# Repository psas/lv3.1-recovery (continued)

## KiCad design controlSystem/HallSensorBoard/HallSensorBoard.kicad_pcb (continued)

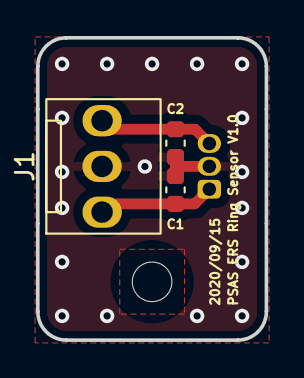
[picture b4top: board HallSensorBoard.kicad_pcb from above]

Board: 2 copper layers, 12.7 x 16.8 mm, 4 parts (1 on the bottom side), 3 nets.

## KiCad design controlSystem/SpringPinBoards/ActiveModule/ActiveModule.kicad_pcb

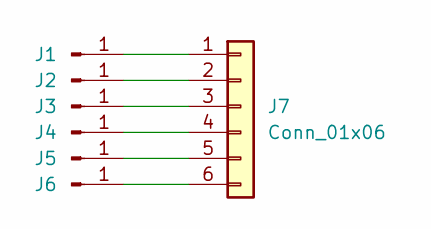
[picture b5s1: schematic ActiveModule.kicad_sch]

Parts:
J1, J2, J3, J4, J5, J6: Conn_01x01_Male; Mill-Max-0921-5-15-20-77-14-11-0
J7: Conn_01x06; PinHeader_1x06_P2.00mm_Vertical

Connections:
unnamed: J1.1, J7.1
unnamed: J2.1, J7.2
unnamed: J3.1, J7.3
unnamed: J4.1, J7.4
unnamed: J5.1, J7.5
unnamed: J6.1, J7.6

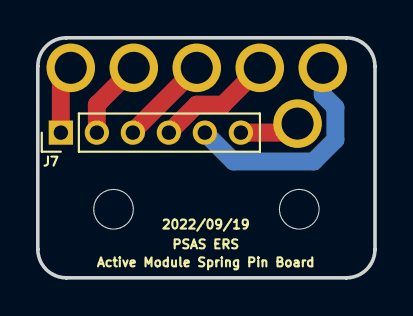
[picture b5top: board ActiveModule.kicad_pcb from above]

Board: 2 copper layers, 18.7 x 13.3 mm, 7 parts (0 on the bottom side), 6 nets.

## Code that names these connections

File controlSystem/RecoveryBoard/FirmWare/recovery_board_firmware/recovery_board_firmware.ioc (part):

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Mcu.Name=STM32F042K(4-6)Tx
Mcu.Package=LQFP32
Mcu.UserName=STM32F042K6Tx
PA1.GPIOParameters=GPIO_Label
PA1.GPIO_Label=LA_POS
PA1.Mode=IN1
PA1.Signal=ADC_IN1
PA11.Mode=Master
PA11.Signal=CAN_RX
PA12.Mode=Master
PA12.Signal=CAN_TX
PA13.Mode=Serial_Wire
PA13.Signal=SYS_SWDIO
PA14.Mode=Serial_Wire
PA14.Signal=SYS_SWCLK
PA15.GPIOParameters=GPIO_ModeDefaultPP,GPIO_Speed,GPIO_PuPd
PA15.GPIO_ModeDefaultPP=GPIO_MODE_AF_PP
PA15.GPIO_PuPd=GPIO_NOPULL
PA15.GPIO_Speed=GPIO_SPEED_FREQ_HIGH
PA15.Mode=Asynchronous
PA15.Signal=USART2_RX
PA2.GPIOParameters=GPIO_ModeDefaultPP,GPIO_Speed,GPIO_PuPd
PA2.GPIO_ModeDefaultPP=GPIO_MODE_AF_PP
PA2.GPIO_PuPd=GPIO_NOPULL
PA2.GPIO_Speed=GPIO_SPEED_FREQ_HIGH
PA2.Mode=Asynchronous
PA2.Signal=USART2_TX
PA3.GPIOParameters=GPIO_PuPd,GPIO_Label,GPIO_Mode
PA3.GPIO_Label=ISO_CHUTE
PA3.GPIO_Mode=GPIO_MODE_INPUT
PA3.GPIO_PuPd=GPIO_NOPULL
PA3.Signal=GPIO_Input
PA4.GPIOParameters=GPIO_PuPd,GPIO_Label,GPIO_Mode
PA4.GPIO_Label=ISO_DROGUE
PA4.GPIO_Mode=GPIO_MODE_INPUT
PA4.GPIO_PuPd=GPIO_NOPULL
PA4.Signal=GPIO_Input
PA5.GPIOParameters=GPIO_Speed,PinState,GPIO_PuPd,GPIO_Label,GPIO_ModeDefaultOutputPP
PA5.GPIO_Label=DCM_DIR
PA5.GPIO_ModeDefaultOutputPP=GPIO_MODE_OUTPUT_PP
PA5.GPIO_PuPd=GPIO_NOPULL
PA5.GPIO_Speed=GPIO_SPEED_FREQ_LOW
PA5.PinState=GPIO_PIN_RESET
PA5.Signal=GPIO_Output
PA6.GPIOParameters=GPIO_Label
PA6.GPIO_Label=DCM_PWM
PA6.Signal=S_TIM3_CH1
PA7.GPIOParameters=GPIO_Speed,PinState,GPIO_PuPd,GPIO_Label,GPIO_ModeDefaultOutputPP
PA7.GPIO_Label=DCM_ON
PA7.GPIO_ModeDefaultOutputPP=GPIO_MODE_OUTPUT_PP
PA7.GPIO_PuPd=GPIO_NOPULL
PA7.GPIO_Speed=GPIO_SPEED_FREQ_LOW
PA7.PinState=GPIO_PIN_RESET
PA7.Signal=GPIO_Output
PA8.GPIOParameters=GPIO_Speed,PinState,GPIO_PuPd,GPIO_Label,GPIO_ModeDefaultOutputPP
PA8.GPIO_Label=LA_IN1
PA8.GPIO_ModeDefaultOutputPP=GPIO_MODE_OUTPUT_PP
PA8.GPIO_PuPd=GPIO_NOPULL
PA8.GPIO_Speed=GPIO_SPEED_FREQ_LOW
PA8.PinState=GPIO_PIN_RESET
PA8.Signal=GPIO_Output
PA9.GPIOParameters=GPIO_Speed,GPIO_FMA9,PinState,GPIO_PuPd,GPIO_Label,GPIO_ModeDefaultOutputPP
PA9.GPIO_FMA9=__NULL
PA9.GPIO_Label=LA_IN2
PA9.GPIO_ModeDefaultOutputPP=GPIO_MODE_OUTPUT_PP
PA9.GPIO_PuPd=GPIO_NOPULL
PA9.GPIO_Speed=GPIO_SPEED_FREQ_LOW
PA9.PinState=GPIO_PIN_RESET
PA9.Signal=GPIO_Output
PB0.GPIOParameters=GPIO_Speed,PinState,GPIO_PuPd,GPIO_Label,GPIO_ModeDefaultOutputPP
PB0.GPIO_Label=LED
PB0.GPIO_ModeDefaultOutputPP=GPIO_MODE_OUTPUT_PP
PB0.GPIO_PuPd=GPIO_NOPULL
PB0.GPIO_Speed=GPIO_SPEED_FREQ_LOW
PB0.PinState=GPIO_PIN_RESET
PB0.Signal=GPIO_Output
PB1.GPIOParameters=GPIO_Label
PB1.GPIO_Label=BATT_READ
PB1.Mode=IN9
PB1.Signal=ADC_IN9
PB3.GPIOParameters=GPIO_Speed,PinState,GPIO_PuPd,GPIO_Label,GPIO_ModeDefaultOutputPP
PB3.GPIO_Label=SENSOR_ON
PB3.GPIO_ModeDefaultOutputPP=GPIO_MODE_OUTPUT_PP
PB3.GPIO_PuPd=GPIO_NOPULL
PB3.GPIO_Speed=GPIO_SPEED_FREQ_LOW
PB3.PinState=GPIO_PIN_RESET
PB3.Signal=GPIO_Output
PB4.GPIOParameters=GPIO_Label
PB4.GPIO_Label=SENSOR2
PB4.Signal=GPIO_Input
PB5.GPIOParameters=GPIO_PuPd,GPIO_Label,GPIO_Mode
PB5.GPIO_Label=SENSOR1
PB5.GPIO_Mode=GPIO_MODE_INPUT
PB5.GPIO_PuPd=GPIO_NOPULL
PB5.Signal=GPIO_Input
PB7.GPIOParameters=GPIO_Speed,PinState,GPIO_PuPd,GPIO_Label,GPIO_ModeDefaultOutputPP,GPIO_FM7
PB7.GPIO_FM7=__NULL
PB7.GPIO_Label=ACOK
PB7.GPIO_ModeDefaultOutputPP=GPIO_MODE_OUTPUT_PP
PB7.GPIO_PuPd=GPIO_NOPULL
PB7.GPIO_Speed=GPIO_SPEED_FREQ_LOW
PB7.PinState=GPIO_PIN_RESET
PB7.Signal=GPIO_Output
PB8.GPIOParameters=GPIO_Label
PB8.GPIO_Label=SPKR
PB8.Signal=S_TIM16_CH1
PF0-OSC_IN.Mode=HSE-External-Clock-Source
PF0-OSC_IN.Signal=RCC_OSC_IN
RCC.SYSCLKFreq_VALUE=8000000
board=NUCLEO-F042K6
boardIOC=true

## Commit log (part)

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2025-10-31 Fix bug in can_reader
    The conditional compilation scope should be around this entire arm of
    the match statement, otherwise the main board will send out the drogue
    acknowledgement message
2025-10-31 Rename TELEMETRUM_HEARTBEAT_ID -> SENDER_HEARTBEAT_ID
    It's not the telemetrum that sends the heartbeat its the sender board
2025-11-01 Write README for src/bin
2025-11-01 Rename *_STATUS_ID -> *_HEARTBEAT_ID
    Clarity
2025-11-01 Move motor consts to motor module
2025-11-01 Write src README.md
    README explains the shared modules found in src dir
    Fix typo
2025-11-01 Update py can testing scripts
2025-11-01 rename test_can.py -> echo_can.py
    pytest looks for files named test_*.py, so this would conflict with it's
    usage. Also, this is just a clearer name for the purpose of the script
2025-11-02 Write pytests to verify acknowledgement of deployment CAN messages
    These two tests should send messages to the drogue and main boards and
    verify they respond with appropriate acknowledgement messages.
2025-11-02 update gitignore to ignore pycache
2025-11-02 Update src/bin/README.md
    parachute motor constants moved to src/motor.rs
2025-11-02 Update src/README.md
    echo_can task to be used with echo_can.py, not test_can.py
2025-11-02 Fix buffer overflow when recording motor_isense csv
    If the motor runs for longer than expected the buffer holding the csv
    values can overflow. I added a check that makes sure that wont happen
2025-11-07 Add flash memory storage of motor actuations
    Create a flash driver and mutex and use it to store the number of times
    the motor has been actuated. Create cli commands to print and erase this
    data.
2025-11-13 use BOARD env var instead of feature flags to manage parachute boards
    Instead of using feature flags, which aren't supposed to be mutually
    exclusive, use the BOARD environment variable to flash the parachute
    image to either the main or the drogue board. For the main board, set
    BOARD = "main", or for the drogue board set BOARD = "drogue"
2025-11-13 Make reading the ring position non_blocking
    Using try_get instead of changed when reading the ring position will
    allow the heartbeat and "pos" cli command to tell users that the ring is
    not yet intialized instead of blocking until it is initialized.
2025-11-13 Add embedded-test crate and config
    Embedded test is probe-rs's testing suite for running tests on board.
    This commit adds the crate with some necessary configs in the Cargo.toml
    as well as creates a tests directory, blinky sample test, and adds the
    necessary linker args to the build.rs file.
2025-11-20 Make flashing drogue vs main board easier
    Instead of hard coding the environment variable in .cargo/config.toml,
    you can now specify the BOARD environment variable through a commmand
    line override. This was previously not possible because setting it
    through the command line wouldnt trigger a rerun of the build. Adjusting
    the build.rs file fixed this issue. I also wrote cargo aliases to
    simplify the flash commands, and updated the READMEs.
2025-12-28 fix typo
    Config.toml should've been Cargo.toml
2025-12-28 Update README
    Clarify that there is no separate build command to call when
    building/flashing, but add build command if needed.
2026-01-27 variable renames for clarity, update shorepow state in sender
2026-02-04 add parachute boards status ok as dependency to rocket ready
2026-02-04 state of ers boards was using incorrect bit
    0 is the ring position, 5 is the ready state
2026-02-04 make status messages for ers status clearer
    ERR doesn't really make sense. ok or not ready is clearer.
2026-02-04 Fix ers ready state
    position 2 is inbetween, 3 is locked
2026-02-04 display the sensor state when pos uart command is executed
    the uart pos command will now show both the raw adc values as well as
    the calculated ring state of those values for debugging purposes
2026-02-11 Fix RocketReady logic
2026-02-17 Update state commands on all boards
    Now there is an Id field for each board that will print its name, which
    is different from how the chute boards were before. They would only
    print a number and the sender didn't have a id field at all. Keep in
    mind the sender doesnt have an actual field in its state for this
    because its static. I also print a delta from the last seen values
    rather than a time stamp so you dont have to do the math in your head
2026-03-03 Store sensor limits in flash and add cli cmd to change or print them
2026-03-03 Update Readmes
2026-03-23 enable independent watchdog on all 3 boards
    iwdg to recover from hard crashes
2026-03-23 change wdg timing to be more reasonable
2026-03-24 Use buffered CAN driver
    There are some arcane transient errors happening once every 15 to 20
    avionics system tests where the sender will not send a CAN message in
    response to the telemetrum signal to deploy. Buffered CAN should be more
    resilient in theory and so might help with this issue.
2026-03-30 upgrade crates and refactor
2026-03-31 Bugfix: Drogue not releasing reliably in resp to CAN msg
    drogue was releasing slowly or sometimes not at all when CAN messages
    were sent to it. I discovered the motor mutex was not being released
    because there was no inner scope, so I added one. I also moved the
    acknowledge CAN messages for both parachute boards to after the
    deployment happens because drogue was acknowledging even when it didnt
    release. These changes seem to fix the bug.
2026-04-01 bugfix: sender not sending CAN messages reliably
    the parachute boards were sending multiple acknowledgment messages. the
    sender would reset the acknowledgment atomic to false, but then
    immediately set it back to true. We also use a signal instead of a watch
    for the motor i_sense hoping to avoid it immediately returning
    read_until_pos due to stale values in the watch.
2026-04-02 Better error handling
    rather than call .unwrap() on things, I have gone through and tried to
    propagate errors and handle them instead. When unwrap or expect is the
    simplest option, I've replaced them with defmt's unwrap instead of the
    builtin as it should use less resources.
2026-04-02 bugfix: sender heartbeat CAN spam
    I was checking the wrong time for whether or not to send the heartbeat
    message. Changed to time_now and it fixed the error
2026-04-02 bugfix: fix inverted shore power on logic
    high means shorepower is off, low means it's on
2026-04-02 bugfix: unlocking ring when shore power is on
    this is maybe not a "bug" but it is a safety concern. we should never be
    unlocking th rings when shorepower is on. this prevents that.
2026-04-02 move motor ring pos receiver into ::new function
    we don't need to recreate the ring pos receiver every time we run the
    motor. this is a minor optimization but anything to keep the motor
    running operation as lean as possible is a good thing in my opinion.
2026-04-02 run broadcast_ring_position task more often
    this may or may not be necessary but since running the motor will wait
    for this task, doing it more often seems smart
2026-04-02 clean up info logs
2026-04-25 bugfix/rocket ready logic error
    Fix two errors where rocket ready was assumed to be active high, but
    it's actually active low. This was being masked by another error where
    rocket ready was being asserted when shorepower was on.
2026-05-04 Overhaul docs
    The docs were not good before. Also they became heavily out of date over
    time. I've reduced their verbosity as much as I could, and moved as much
    of the explanations of things to comments and the tops of modules.
2026-05-04 create DISABLE_BEEP environment variable
    The beeps will now be on by default but can be turned off by flashing
    with DISABLE_BEEP=true
2026-05-04 More docs clean up
2026-05-04 fix bug with disable_beep cfg
    forgot to make buzz_mode mut, linter didnt care because it doesnt use
    cfgs so it never thought it was being changed. also suppress some lints
    that occur because of cfg directives. Tested and working as normal on
    sender board
2026-05-06 bugfix, CAN deploy message
    We should ignore the 100us continuity check the stratologger does when
    powering off. Also, panicing when there's an error sending the can
    deploy message is not a good idea, for now just log the error and keep
    going.
2026-05-06 remove all calls to panic!()
2026-05-08 Fix bugs preventing flashing
    Mostly just syntax errors, but I will need to figure out how to not
    panic inside the error handler when making the strings for the limits
    command
2026-05-08 Fix freezing when CAN bus is down bug
    When the CAN bus is down, if the telemetrum fires it will hold on to the
    shore power pin mutex until it can send a can message. The main thread
    will wait until it can unlock this mutex before it does anything else so
    that it can update state. this means if the CAN bus can't send the
    deploy message, nothing else can happen.
2026-05-13 Log ignoring sub 10ms firing signal
